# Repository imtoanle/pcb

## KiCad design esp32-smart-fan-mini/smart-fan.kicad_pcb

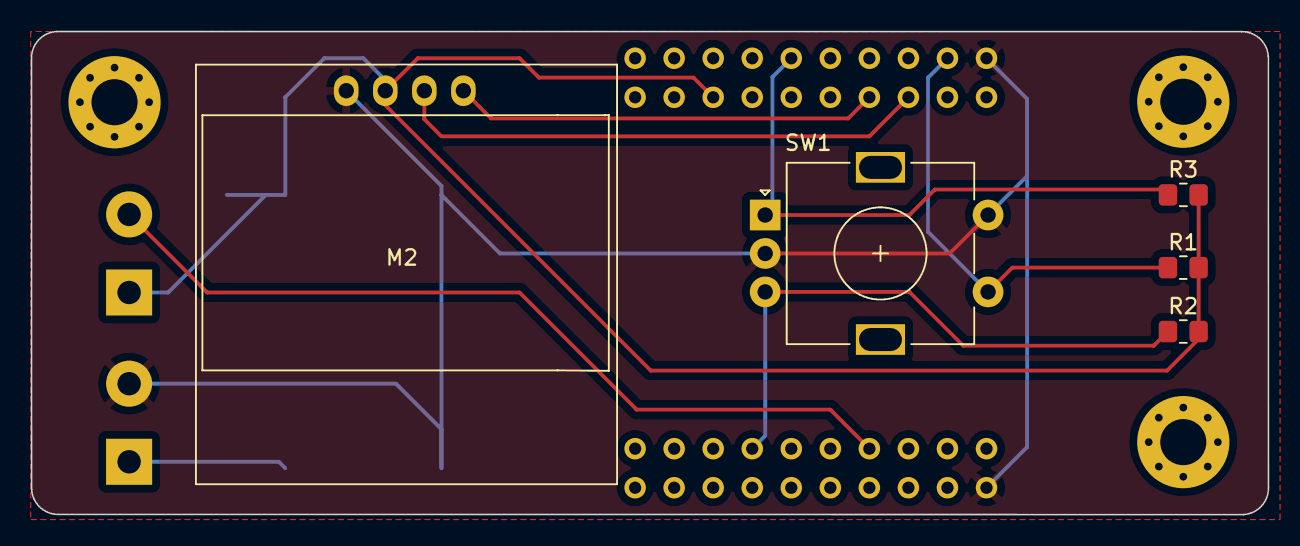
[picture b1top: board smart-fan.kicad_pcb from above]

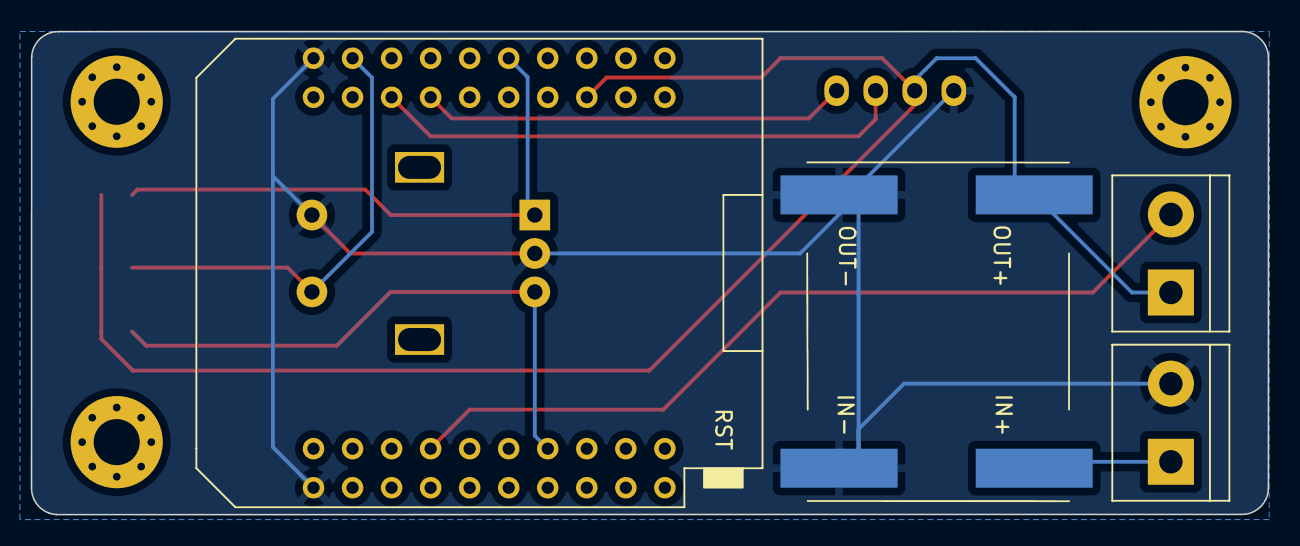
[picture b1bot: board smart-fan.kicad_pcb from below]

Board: 2 copper layers, 80.5 x 31.4 mm, 12 parts (4 on the bottom side), 9 nets.

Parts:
H1, H2, H3: MountingHole_3mm_Pad_Via
J1, J6: Screw_Terminal_01x02; TerminalBlock_bornier-2_P5.08mm
M1: MP1584-Module; MP1584_Module_Nopad
M2: SSD1306-128x64OLED
R1, R2, R3: R; R_0805_2012Metric_Pad1.20x1.40mm_HandSolder
SW1: RotaryEncoder_Switch; RotaryEncoder_Alps_EC11E-Switch_Vertical_H20mm
U1: mini_esp32; esp32-wemos-d1-mini

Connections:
5V: J1.1, M1.3 (Vout+), M2.2 (VDD), R1.2, R2.2, R3.2, U1.35 (VCC_(USB))
24V: J6.1, M1.1 (Vin+)
GND: J6.2, M1.2 (Vin-), M1.4 (Vout-), M2.1 (GND), SW1.C, SW1.S2, U1.1 (GND), U1.22 (GND)
IO4: R3.1, SW1.A, U1.32 (IO_04)
IO5: R2.1, SW1.B, U1.14 (IO_05/D8)
IO18: J1.2, U1.8 (IO_18/D5)
unnamed: M2.3 (SCL), U1.25 (IO_22/D1/SCL)
unnamed: M2.4 (SDA), U1.27 (IO_21/D2/SDA)
unnamed: R1.1, SW1.S1, U1.24 (IO_27)

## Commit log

2023-12-17 Add ESP32 smart fan mini board
2023-12-17 Update panalize
